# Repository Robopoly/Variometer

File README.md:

# Variometer
Un variometre programmé en arduino   
  
Le principe de celui est d'indiquer la vitesse verticale à son utilisateur, appareil très utilisé par les pilotes de planeurs ou parapentes pour trouver les courants ascendants.    
Le variometre produits des bips en fonctions de la vitesse, plus celle-ci est élévée plus les bips sont rapprochés et aigus.  
Des bips plus graves indiquent que l'on se trouve dans un courant descendant.  
Le variometre dispose également d'un mode vibreur activable via un bouton : le moteur vibrant s'active lorsqu'on monte

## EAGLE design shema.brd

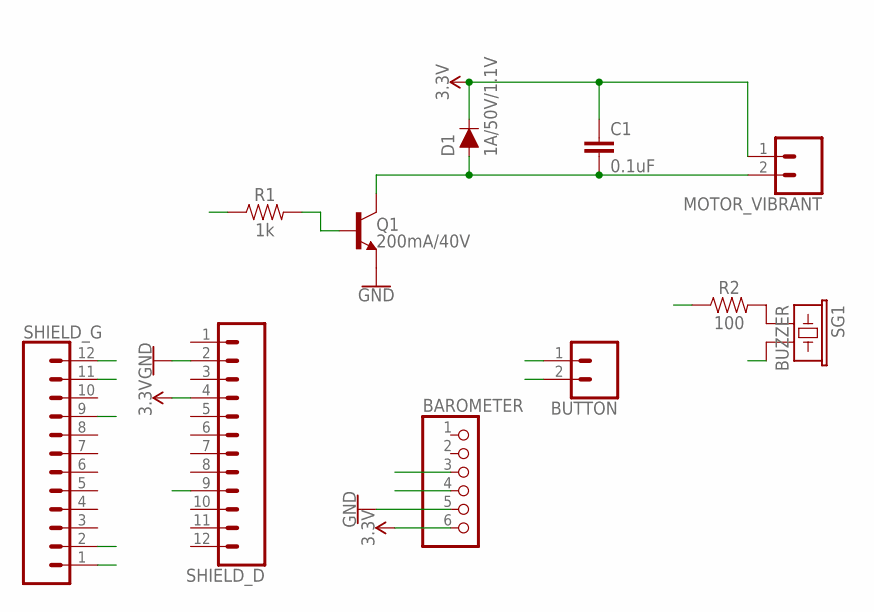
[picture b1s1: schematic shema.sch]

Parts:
BAROMETER: PINHD-1X6; 1X06
BUTTON: CONN_02; 1X02
C1: 0.1uF; CAP-PTH-SMALL-KIT
D1: 1A/50V/1.1V; DIODE-1N4001
MOTOR_VIBRANT: CONN_02; 1X02
Q1: 200mA/40V; TO-92
R1: 1k; AXIAL-0.3
R2: 100; AXIAL-0.3EZ
SG1: BUZZER; PS1240P02BT
SHIELD_D: CONN_12; 1X12
SHIELD_G: CONN_12; 1X12

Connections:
AUDIO0: SG1.P$2 (2), SHIELD_G.12
AUDIO1: R2.P$1 (1), SHIELD_G.11
BUTTON: BUTTON.2, SHIELD_D.9
GND: BAROMETER.5, BUTTON.1, Q1.1 (E), SHIELD_D.2
MOTOR_CONTROL: R1.P$1 (1), SHIELD_G.9
unnamed: C1.2, D1.A, MOTOR_VIBRANT.2, Q1.3 (C)
unnamed: R2.P$2 (2), SG1.P$1 (1)
SCL: BAROMETER.4, SHIELD_G.1
SDA: BAROMETER.3, SHIELD_G.2
VCC: BAROMETER.6, C1.1, D1.C, MOTOR_VIBRANT.1, SHIELD_D.4
ZBRA: Q1.2 (B), R1.P$2 (2)

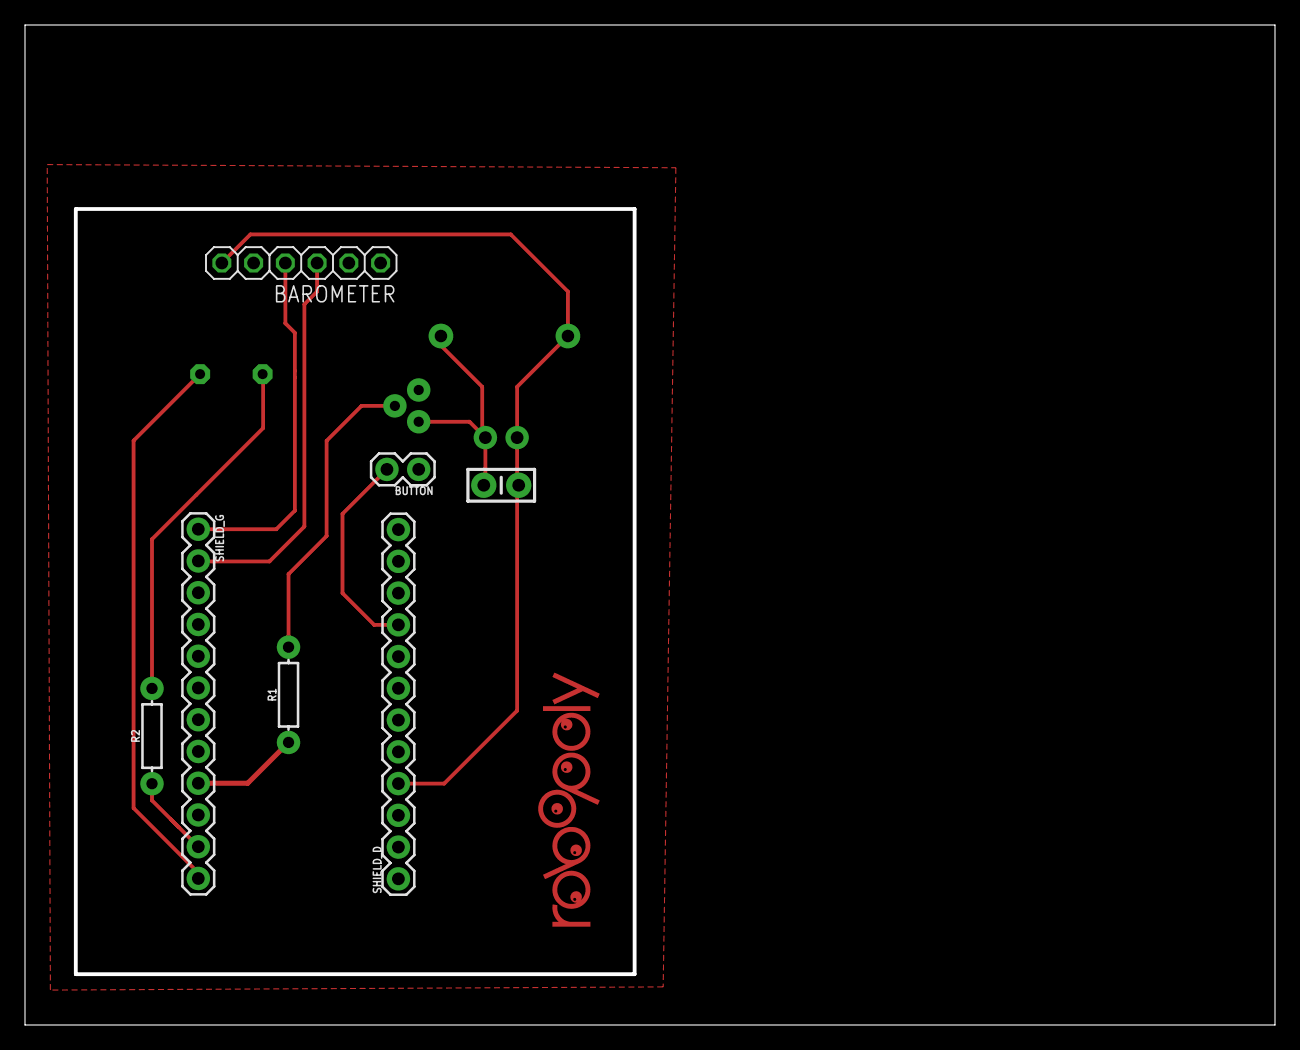
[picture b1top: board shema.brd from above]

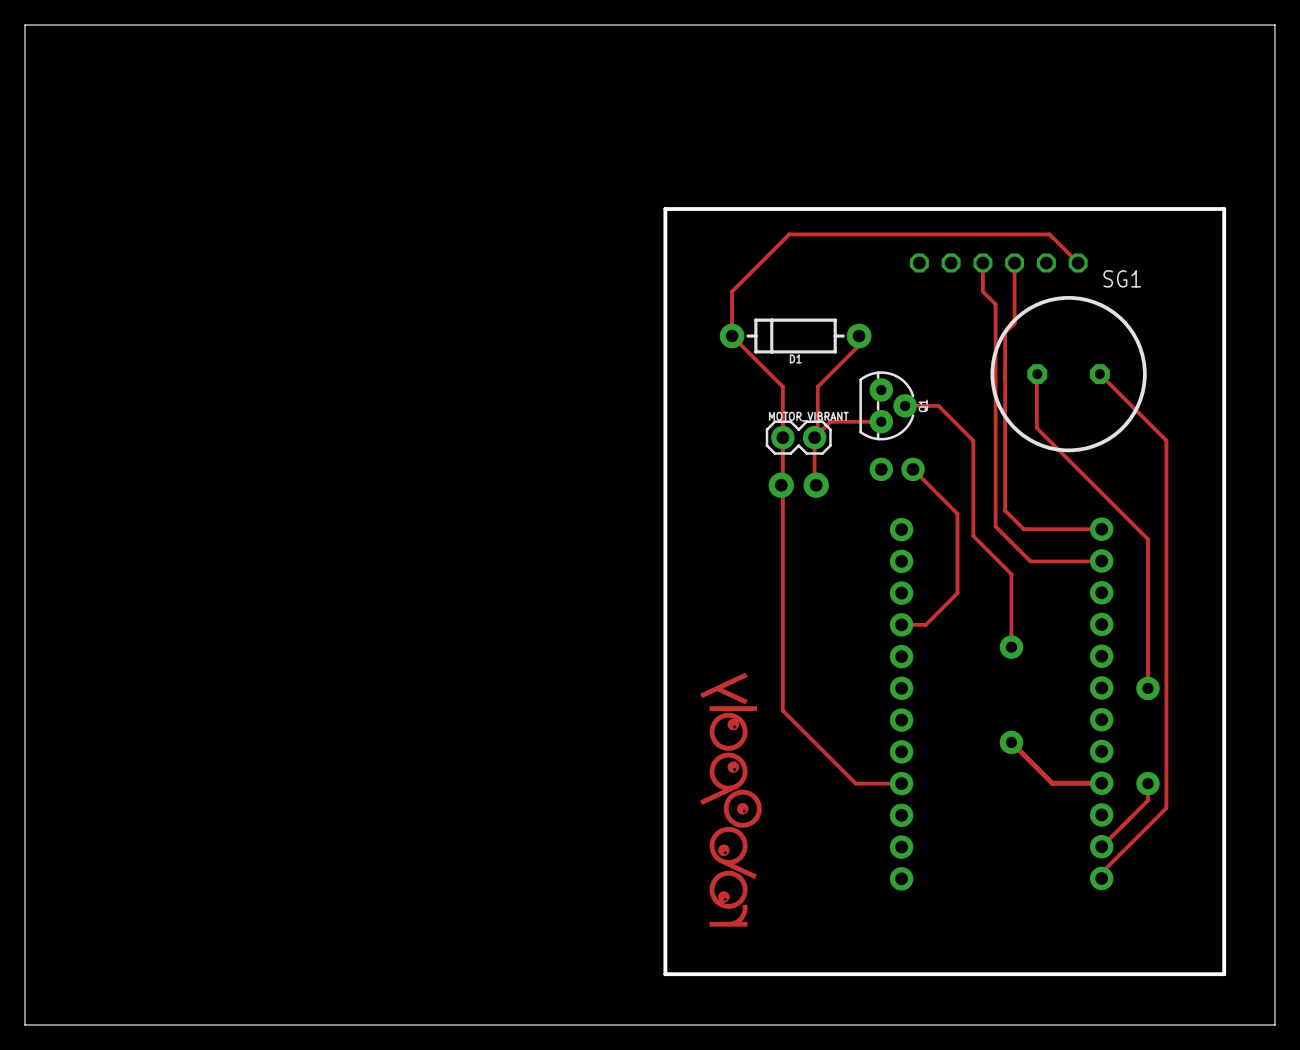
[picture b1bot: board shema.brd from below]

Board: 2 copper layers, 100.0 x 80.0 mm, 12 parts (4 on the bottom side), 11 nets.

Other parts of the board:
U$1: ROBOPOLY-LOGO-SYMBOL

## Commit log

2018-03-04 Create materiel
2018-03-04 Rename materiel to materiel.md
2018-03-06 jkj
    lkjlkj
2018-03-11 Eagle Files
    Eagle Files

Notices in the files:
parts and their libraries:
SparkFun-DiscreteSemi: Licensing: Creative Commons ShareAlike 4.0 International - https://creativecommons.org/licenses/by-sa/4.0
